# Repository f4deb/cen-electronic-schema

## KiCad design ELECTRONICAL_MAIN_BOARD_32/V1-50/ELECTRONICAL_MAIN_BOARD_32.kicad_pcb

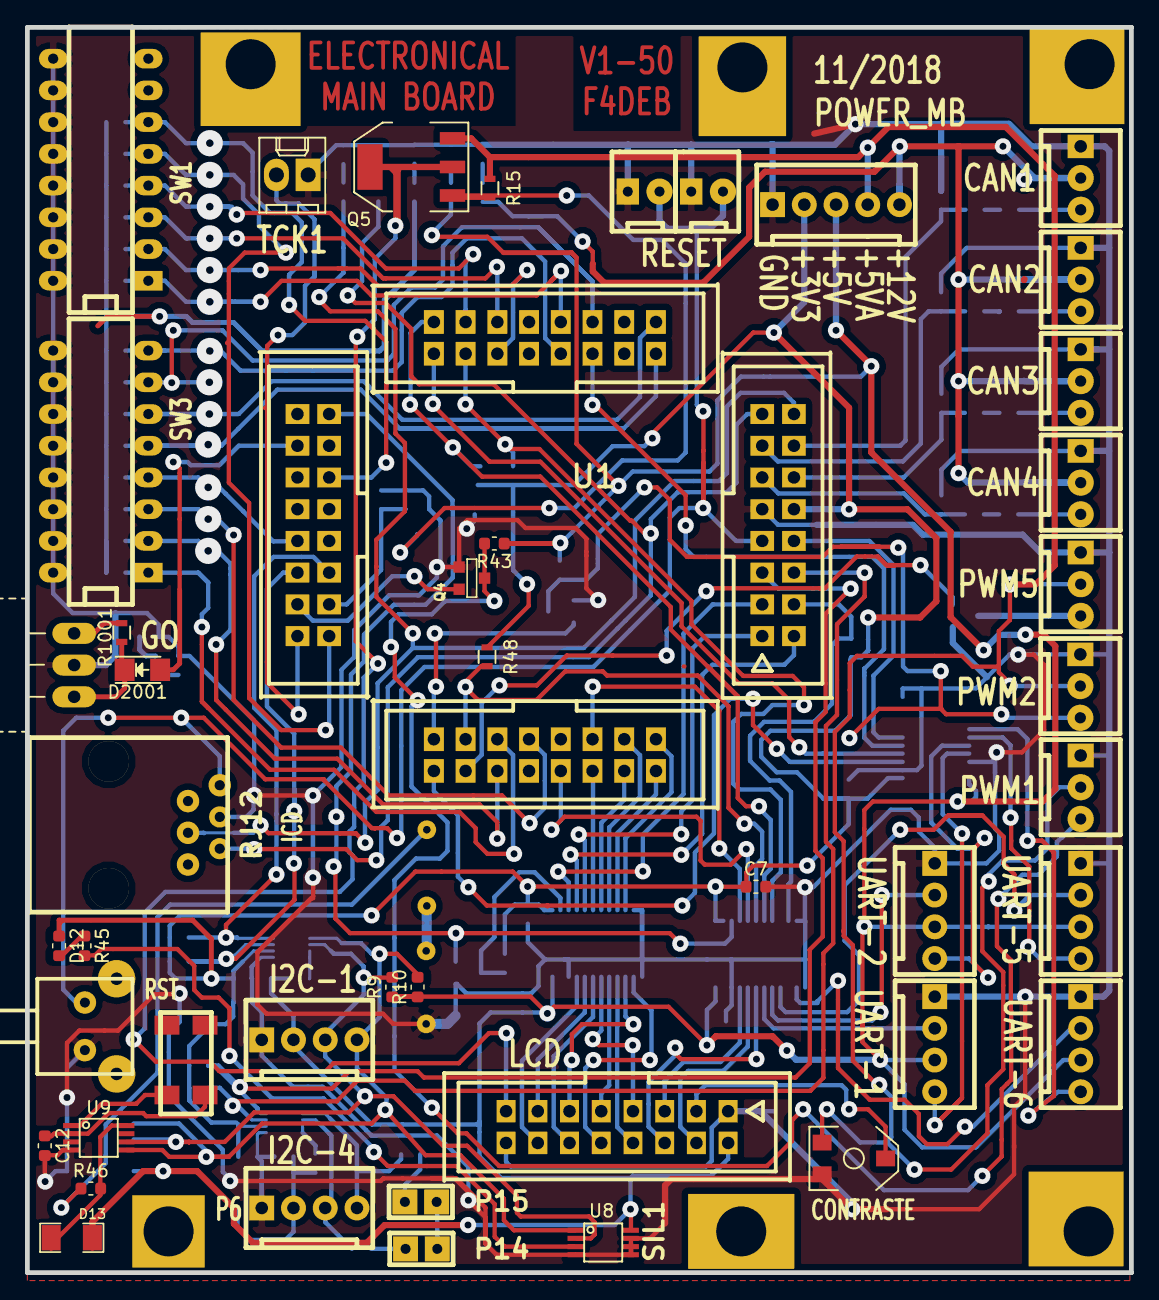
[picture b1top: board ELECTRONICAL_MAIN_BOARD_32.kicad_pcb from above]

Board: 2 copper layers, 88.4 x 99.7 mm, 126 parts (0 on the bottom side), 112 nets.

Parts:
C1, C2, C3, C4, C5, C6, C7, C8, C10, C11: 100n; C_0603_1608Metric
C9, C13: 10F; C-10F
C12: C; C_0603_1608Metric
D1, D2, D3, D4, D5, D7, D8, D9, D10, D11: LED; LED_0603_1608Metric
D12: LED; R_0603_1608Metric
D13: DIODESCH; SM1206
D2001: LED; LED_1206
J1, J2, J3, J4, J6, J7: SIL1; COLONETTE
J5: RJ12; RJ12_E
K1, K2, K3, K4, K5, K6, K7: CONN_3; KK-3
K8: CONN_2; Molex_KK_6410-02
P1: HE10-16; he10-16d
P2, P3, P4, P5, P6, P7: CONN_4; KK-4
P9: CONN_5; KK-5
P10, P11: CONN_2; KK-2
P14, P15: CAVALIER
Q1, Q2, Q3, Q4: BSS123; SOT23EBC
Q5: IRFL9014TRPBF; SOT-223
Q6: 2N7002; SOT-23
R1, R9, R10, R13, R14: 1k; R_0603_1608Metric
R2, R3, R4, R6, R45: 330; R_0603_1608Metric
R5, R16, R17, R18, R19, R20, R21, R22, R23, R24, R25, R26, R27, R28, R29: 10K; R_0603_1608Metric
R7, R8, R11, R12: 2.1k; R_0603_1608Metric
R15, R48, R49, R50, R51: 10k; R_0603
R30, R31, R32, R33: 3.2k; R_0603_1608Metric
R34, R35, R36, R37: 1.5k; R_0603_1608Metric
R38, R39: 220k; R_0603_1608Metric
R40, R41, R42, R43: 4.7k; R_0603_1608Metric
R44: 3..3k; R_0603_1608Metric
R46: 150; R_0603_1608Metric
R47: 100k; R_0603
R1001: 1k; R_0603
RVAR1: 4.7K; POT_SMD
SW1, SW3: SWITCH_X_8; DIP-16__300_ELL
SW2: SW_PUSH_SMALL; SW
U1: PIC32MX795F512H; PIC32½64
U2, U3, U6: 74LVCC3245; SSOP24
U4, U5: PCA9306; VSSOP-8
U7: 24C512; SOIC-8_3.9x4.9mm_P1.27mm
U8: LM75A; SSOP8
U9: PCF8563; SSOP8
U1001: HALL-U18; TO-220_Neutral123_Horizontal_MountedFromLS_LargePads
X1: CRYSTAL1; LFXTAL003000

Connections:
+3V3: C1.1, C2.1, C3.1, C7.1, C8.1, D12.1, J5.2, P9.2, R2.1, R7.1, R8.1, R11.1, R12.1, R16.1, R17.1, R18.1, R19.1, R20.1, R21.1, R22.1, R23.1, R24.1, R25.1, R26.1, R27.1, R28.1, R29.1, R42.1, R48.1, R49.1, R50.1, R51.1, U1.10, U2.1, U2.2, U3.1, U4.2, U5.2, U6.1
+5V: C4.1, C5.1, C6.1, C10.1, C11.1, D13.1, P1.2, P2.3, P3.3, P4.3, P5.3, P6.2, P7.2, P9.3, P14.2, P15.2, R1.1, R9.1, R10.1, R38.1, R39.1, R40.1, R41.1, R43.1, U2.24, U3.24, U6.24, U7.8, U8.8
+5VA: K5.2, K6.2, K7.2, P9.4, Q5.3, R15.1, RVAR1.1
+5VD: R1001.1, U1001.1
+12V: K1.2, K2.2, K3.2, K4.2, P9.5, R44.1
/5vto3v3/D0: U1.60, U6.6
/5vto3v3/D1: U1.61, U6.8
/5vto3v3/D2: U1.62, U6.7
/5vto3v3/D3: U1.63, U6.10
/5vto3v3/D4: U1.64, U6.9
/5vto3v3/D5: U1.1, U6.5
/5vto3v3/D6: U1.2, U6.4
/5vto3v3/D7: U1.3, U6.3
/5vto3v3/E: U1.58, U2.5
/5vto3v3/OC1: Q4.1, U1.46
/5vto3v3/OC1-5V: K5.3, Q4.3, R43.2
/5vto3v3/OC2: Q1.1, U1.49
/5vto3v3/OC2-5V: K6.3, Q1.3, R40.2
/5vto3v3/OC5: Q2.1, U1.52
/5vto3v3/OC5-5V: K7.3, Q2.3, R41.2
/5vto3v3/RS: U1.59, U2.4
/5vto3v3/RW: Q3.1, U1.33, U2.3
/5vto3v3/SCL1: R8.2, U1.44, U4.3
/5vto3v3/SCL4: R12.2, U1.6, U5.3
/5vto3v3/SCL4-5V: P6.3, R13.2, U5.6
/5vto3v3/SDA1: R7.2, U1.43, U4.4
/5vto3v3/SDA4: R11.2, U1.5, U5.4
/5vto3v3/SDA4-5V: P6.4, R14.2, U5.5
/5vto3v3/U1RX: U1.50, U3.3
/5vto3v3/U1RX-5V: P2.4, U3.21
/5vto3v3/U1TX: R48.2, U1.51, U2.6
/5vto3v3/U1TX-5V: P2.2, U2.18
/5vto3v3/U2RX: U1.31, U3.4
/5vto3v3/U2RX-5V: P3.4, U3.20
/5vto3v3/U2TX: R49.2, U1.32, U2.7
/5vto3v3/U2TX-5V: P3.2, U2.17
/5vto3v3/U5RX: U1.21, U3.5
/5vto3v3/U5RX-5V: P4.4, U3.19
/5vto3v3/U5TX: R50.2, U1.29, U2.8
/5vto3v3/U5TX-5V: P4.2, U2.16
/5vto3v3/U6RX: U1.8, U3.6
/5vto3v3/U6RX-5V: P5.4, U3.18
/5vto3v3/U6TX: R51.2, U1.4, U2.10
/5vto3v3/U6TX-5V: P5.2, U2.14
/BD0: P1.7, U6.18
/BD1: P1.8, U6.16
/BD2: P1.9, U6.17
/BD3: P1.10, U6.14
/BD4: P1.11, U6.15
/BD5: P1.12, U6.19
/BD6: P1.13, U6.20
/BD7: P1.14, U6.21
/BE: P1.6, U2.19
/BRS: P1.4, U2.20
/BRW: P1.5, U2.21
/CONT: P1.3, RVAR1.2
/PIC32/CAN1: D7.1, K1.3
/PIC32/CAN2: D8.1, K2.3
/PIC32/CAN3: D9.1, K3.3
/PIC32/CAN4: D10.1, K4.3
/PIC32/GO: D2001.1, R1001.2, U1001.3
/PIC32/LED1: D2.1, R3.2
/PIC32/LED2: D1.1, R4.2
/PIC32/PGEC1: J5.5, R4.1, U1.15
/PIC32/PGED1: J5.4, R3.1, U1.16
/PIC32/RST: J5.1, P10.2, P11.2, SW2.2, U1.7
/PIC32/SW0: R26.2, SW3.1, U1.53
/PIC32/SW1: R27.2, SW3.2, U1.54
/PIC32/SW2: R28.2, SW3.3, U1.55
/PIC32/SW3: R29.2, SW3.4, U1.42
/PIC32/SW4: R16.2, SW3.5, U1.17
/PIC32/SW5: R17.2, SW3.6, U1.18
/PIC32/SW6: R18.2, SW3.7, U1.22
/PIC32/SW7: R19.2, SW3.8, U1.23
/PIC32/SW8: R20.2, SW1.1, U1.24
/PIC32/SW9: R21.2, SW1.2, U1.27
/PIC32/SW10: R22.2, SW1.3, U1.28
/PIC32/SW11: R23.2, SW1.4, U1.30
/PIC32/SW12: R24.2, SW1.5, U1.47
/PIC32/SW13: R25.2, SW1.6, U1.37
/PIC32/T1CK: K8.2, U1.48
/RETRO: P1.15, Q5.2, Q5.4
/SCL1-5V: P7.3, R9.2, U4.6, U7.6, U8.2, U9.6
/SDA1-5V: P7.4, R10.2, U4.5, U7.5, U8.1, U9.5
GND: C1.2, C2.2, C3.2, C4.2, C5.2, C6.2, C7.2, C8.2, C9.2, C10.2, C11.2, C12.2, D1.2, D2.2, D3.2, D4.2, D11.2, J5.3, K1.1, K2.1, K3.1, K4.1, K5.1, K6.1, K7.1, K8.1, P1.1, P1.16, P2.1, P3.1, P4.1, P5.1, P6.1, P7.1, P9.1, P10.1, P11.1, Q1.2, Q2.2, Q3.2, Q4.2, Q6.2, R5.2, R6.2, R34.2, R35.2, R36.2, R37.2, R47.2, RVAR1.3, SW1.9, SW1.10, SW1.11, SW1.12, SW1.13, SW1.14, SW1.15, SW1.16, SW2.1, SW3.9, SW3.10, SW3.11, SW3.12, SW3.13, SW3.14, SW3.15, SW3.16, U1.9, U2.11, U2.12, U2.13, U2.22, U3.2, U3.11, U3.12, U3.13, U3.22, U4.1, U5.1, U6.11, U6.12, U6.13, U6.22, U7.1, U7.2, U7.3, U7.4, U8.4, U8.5, U8.6, U8.7, U9.4, U1001.2
unnamed: C12.1, U9.2, X1.1
unnamed: C13.1, R46.1
unnamed: C9.1, C13.2
unnamed: D3.1, R1.2
unnamed: D4.1, R2.2
unnamed: D5.2, R6.1
unnamed: D7.2, R30.1
unnamed: D8.2, R31.1
unnamed: D9.2, R32.1
unnamed: D10.2, R33.1
unnamed: D11.1, R44.2
unnamed: D12.2, R45.1
unnamed: D13.2, R46.2, U9.8
unnamed: D5.1, D2001.2, R5.1, U1.36
unnamed: P14.1, R13.1
unnamed: P15.1, R14.1
unnamed: Q3.3, R42.2, U6.2
unnamed: Q5.1, Q6.3, R15.2
unnamed: Q6.1, R47.1, U1.45
unnamed: R30.2, R34.1, U1.14
unnamed: R31.2, R35.1, U1.13
unnamed: R32.2, R36.1, U1.12
unnamed: R33.2, R37.1, U1.11
unnamed: R38.2, U4.7, U4.8
unnamed: R39.2, U5.7, U5.8
unnamed: R45.2, U8.3
unnamed: U9.1, X1.2

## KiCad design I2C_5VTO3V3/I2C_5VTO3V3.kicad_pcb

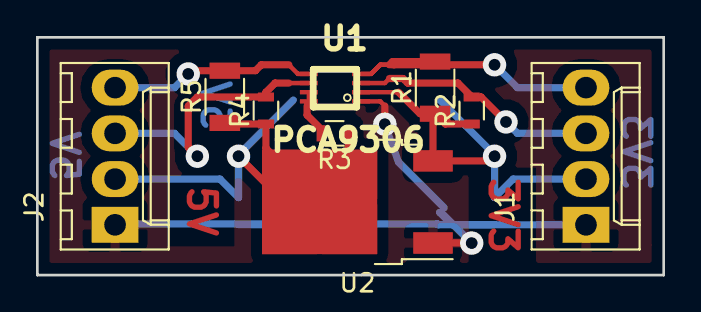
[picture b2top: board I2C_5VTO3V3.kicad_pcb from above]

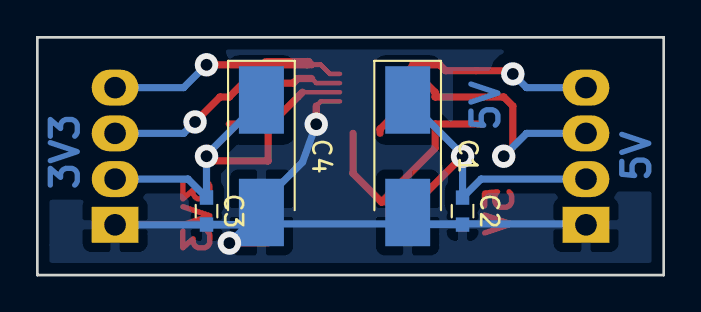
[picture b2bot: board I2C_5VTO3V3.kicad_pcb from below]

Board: 2 copper layers, 34.8 x 13.2 mm, 13 parts (4 on the bottom side), 8 nets.

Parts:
C1, C4: 10U/10V; CP_Tantalum_Case-C_EIA-6032-28_Hand
C2, C3: 100n; C_0603
J1, J2: Conn_01x04; Molex_KK-6410-04_04x2.54mm_Straight
R1, R5: 2.1k; R_1206
R2, R4: 2.1k; R_0603
R3: 220k; R_0603
U1: PCA9306; VSSOP-8
U2: LM1117; TO-252-2

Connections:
+3V3: C3.1, C4.1, J1.2, R1.1, R2.1, U1.2, U2.3
+5V: C1.1, C2.1, J2.2, R3.1, R4.1, R5.1, U2.2
GND: C1.2, C2.2, C3.2, C4.2, J1.1, J2.1, U1.1, U2.1
unnamed: J1.3, R2.2, U1.3
unnamed: J1.4, R1.2, U1.4
unnamed: J2.3, R4.2, U1.6
unnamed: J2.4, R5.2, U1.5
unnamed: R3.2, U1.7, U1.8

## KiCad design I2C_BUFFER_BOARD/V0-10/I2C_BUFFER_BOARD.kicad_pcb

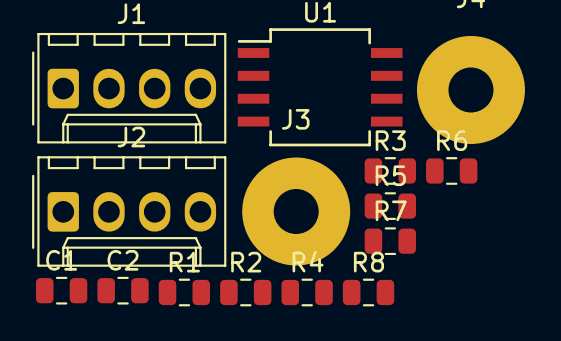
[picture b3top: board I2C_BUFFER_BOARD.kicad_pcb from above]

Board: 2 copper layers, 15 parts (0 on the bottom side), 10 nets, no tracks yet.

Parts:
C1: 100n; C_0805_2012Metric
C2: 1u; C_0805_2012Metric
J1, J2: Conn_01x04_Male; Molex_KK-254_AE-6410-04A_1x04_P2.54mm_Vertical
J3, J4: Conn_01x01_Female; SolderWirePad_1x01_Drill2.5mm
R1, R2, R3, R4: R; R_0805_2012Metric
R5, R6, R7, R8: 0; R_0805_2012Metric
U1: P82B715; SO-8_5.3x6.2mm_P1.27mm

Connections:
unnamed: C1.1, C2.1, J1.2, J2.2, R5.1, R6.1, R7.1, R8.1, U1.8
unnamed: C1.2, C2.2, J1.1, J2.1, U1.4
unnamed: J1.3, R2.2, U1.3
unnamed: J1.4, R1.2, U1.2
unnamed: J2.3, R4.2, U1.6
unnamed: J2.4, R3.2, U1.7
unnamed: R1.1, R5.2
unnamed: R2.1, R6.2
unnamed: R3.1, R7.2
unnamed: R4.1, R8.2

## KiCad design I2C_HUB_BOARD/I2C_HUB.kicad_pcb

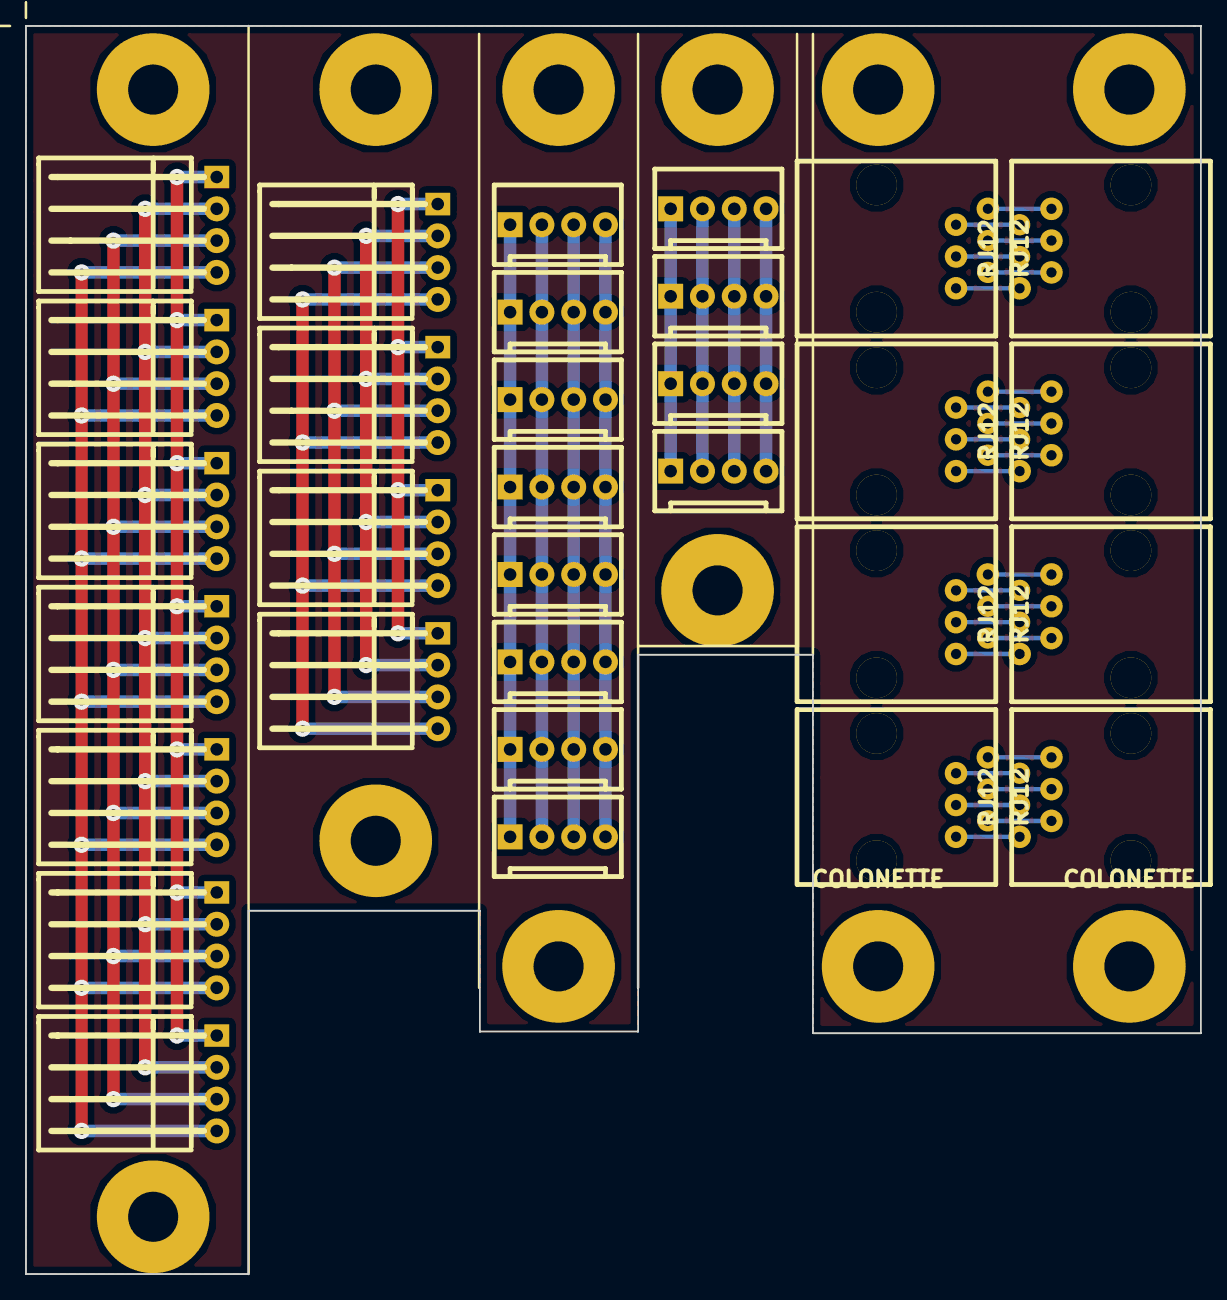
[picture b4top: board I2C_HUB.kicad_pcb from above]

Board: 2 copper layers, 93.9 x 99.7 mm, 43 parts (0 on the bottom side), 40 nets.

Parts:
J1001, J1002, J1003, J1004, J1005, J1006, J1007, J1008: RJ12; RJ12_E
K1001, K1002, K1003, K1004: COLONETTE
P1001, P1002, P1011, P1012, P1021, P1022, P1027, P1028: CONN_01X01; COLONETTE
P1003, P1004, P1005, P1006, P1007, P1008, P1009, P1010, P1023, P1024, P1025, P1026: CONN_01X04; KK-4
P1013, P1015, P1016, P1017, P1018, P1019, P1020, P1029, P1030, P1031, P1032: CONN_01X04; KK-4-H

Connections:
unnamed: J1001.1, J1002.6
unnamed: J1001.2, J1002.5
unnamed: J1001.3, J1002.4
unnamed: J1001.4, J1002.3
unnamed: J1001.5, J1002.2
unnamed: J1001.6, J1002.1
unnamed: J1003.1, J1004.6
unnamed: J1003.2, J1004.5
unnamed: J1003.3, J1004.4
unnamed: J1003.4, J1004.3
unnamed: J1003.5, J1004.2
unnamed: J1003.6, J1004.1
unnamed: J1005.1, J1006.6
unnamed: J1005.2, J1006.5
unnamed: J1005.3, J1006.4
unnamed: J1005.4, J1006.3
unnamed: J1005.5, J1006.2
unnamed: J1005.6, J1006.1
unnamed: J1007.1, J1008.6
unnamed: J1007.2, J1008.5
unnamed: J1007.3, J1008.4
unnamed: J1007.4, J1008.3
unnamed: J1007.5, J1008.2
unnamed: J1007.6, J1008.1
unnamed: P1003.1, P1004.1, P1005.1, P1006.1, P1007.1, P1008.1, P1009.1, P1010.1
unnamed: P1003.2, P1004.2, P1005.2, P1006.2, P1007.2, P1008.2, P1009.2, P1010.2
unnamed: P1003.3, P1004.3, P1005.3, P1006.3, P1007.3, P1008.3, P1009.3, P1010.3
unnamed: P1003.4, P1004.4, P1005.4, P1006.4, P1007.4, P1008.4, P1009.4, P1010.4
unnamed: P1013.1, P1015.1, P1016.1, P1017.1, P1018.1, P1019.1, P1020.1
unnamed: P1013.2, P1015.2, P1016.2, P1017.2, P1018.2, P1019.2, P1020.2
unnamed: P1013.3, P1015.3, P1016.3, P1017.3, P1018.3, P1019.3, P1020.3
unnamed: P1013.4, P1015.4, P1016.4, P1017.4, P1018.4, P1019.4, P1020.4
unnamed: P1023.1, P1024.1, P1025.1, P1026.1
unnamed: P1023.2, P1024.2, P1025.2, P1026.2
unnamed: P1023.3, P1024.3, P1025.3, P1026.3
unnamed: P1023.4, P1024.4, P1025.4, P1026.4
unnamed: P1029.1, P1030.1, P1031.1, P1032.1
unnamed: P1029.2, P1030.2, P1031.2, P1032.2
unnamed: P1029.3, P1030.3, P1031.3, P1032.3
unnamed: P1029.4, P1030.4, P1031.4, P1032.4

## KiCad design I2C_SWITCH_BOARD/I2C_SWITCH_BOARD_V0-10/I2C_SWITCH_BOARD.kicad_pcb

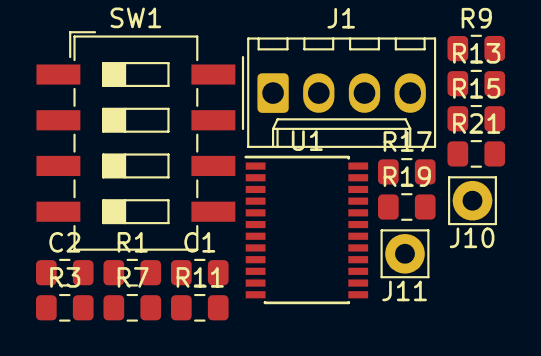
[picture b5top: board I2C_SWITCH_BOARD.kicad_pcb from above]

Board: 2 copper layers, 17 parts (0 on the bottom side), 16 nets, no tracks yet.

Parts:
C1: 100n; C_0805_2012Metric_Pad1.15x1.40mm_HandSolder
C2: 1u; C_0805_2012Metric_Pad1.15x1.40mm_HandSolder
J1: Conn_01x04_Male; Molex_KK-254_AE-6410-04A_1x04_P2.54mm_Vertical
J10, J11: Conn_01x01_Female; Pin_D1.1mm_L8.5mm_W2.5mm_FlatFork
R1, R7, R9, R11, R13, R15, R17, R19, R21: 2.1k; R_0805_2012Metric_Pad1.15x1.40mm_HandSolder
R3: 10k; R_0805_2012Metric_Pad1.15x1.40mm_HandSolder
SW1: SW_DIP_x04; SW_DIP_SPSTx04_Slide_6.7x11.72mm_W8.61mm_P2.54mm_LowProfile
U1: TCA9548APWR; TSSOP-24_4.4x7.8mm_P0.65mm

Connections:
unnamed: C1.1, C2.1, J1.1
unnamed: C1.2, C2.2, J1.2, R1.1, R3.2, R7.1, R9.1, R11.1, R13.1, R15.1, R17.1, R19.1, R21.1, SW1.1, SW1.2, SW1.3, U1.12, U1.24
unnamed: J1.3, R1.2, U1.22
unnamed: J1.4, U1.23
unnamed: R7.2, U1.5
unnamed: R9.2, U1.7
unnamed: R11.2, U1.9
unnamed: R13.2, U1.11
unnamed: R15.2, U1.14
unnamed: R17.2, U1.16
unnamed: R19.2, U1.18
unnamed: R21.2, U1.20
unnamed: SW1.8, U1.21
unnamed: R3.1, U1.3
unnamed: SW1.7, U1.2
unnamed: SW1.6, U1.1

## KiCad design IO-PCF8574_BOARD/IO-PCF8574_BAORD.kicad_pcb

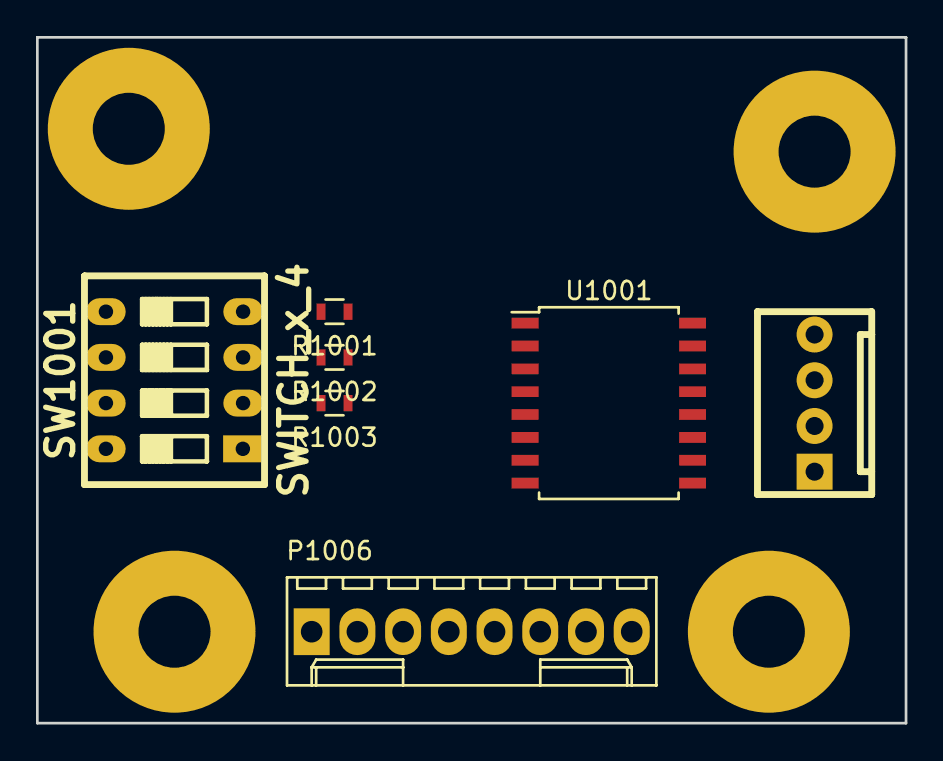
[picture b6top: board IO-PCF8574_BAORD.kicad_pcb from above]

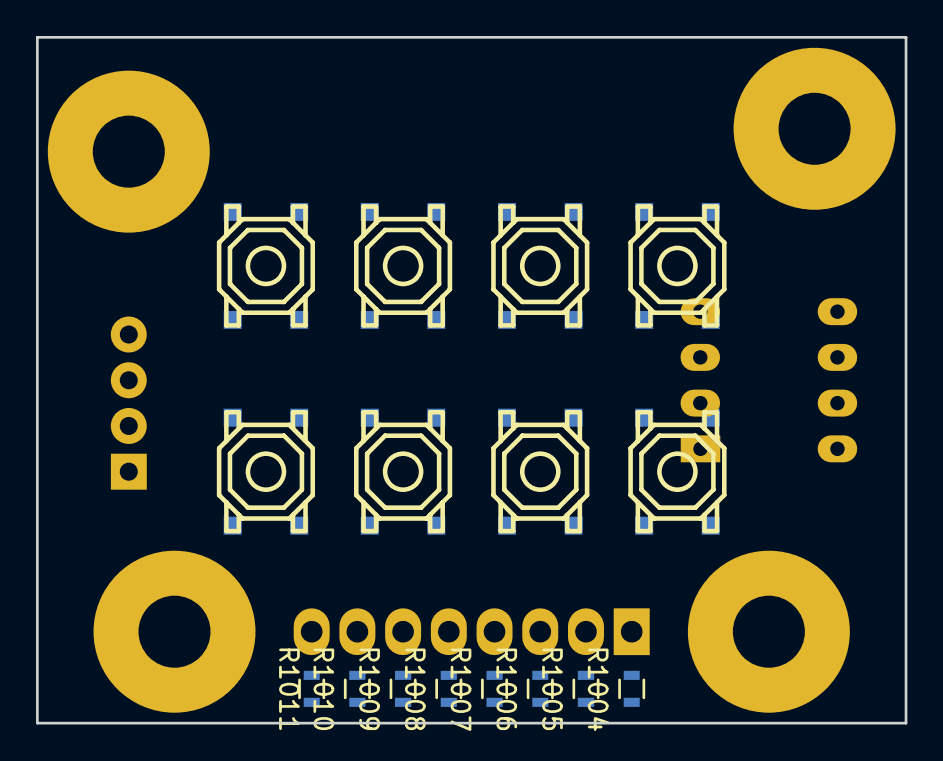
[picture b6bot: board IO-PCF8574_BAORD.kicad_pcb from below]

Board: 2 copper layers, 48.3 x 38.1 mm, 27 parts (16 on the bottom side), 15 nets, no tracks yet.

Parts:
P1001, P1003, P1004, P1005: CONN_01X01; COLONETTE
P1002: CONN_01X04; KK-4
P1006: CONN_01X08; Molex_KK-6410-08_08x2.54mm_Straight
R1001, R1002, R1003, R1004, R1005, R1006, R1007, R1008, R1009, R1010, R1011: 100k; R_0603
SW1001: SWITCH_x_4; dip_4-300
SW1002, SW1003, SW1004, SW1005, SW1006, SW1007, SW1008, SW1009: SW_PUSH_SMALL; smd_push2
U1001: PCF8574A; SOIC-16W_7.5x10.3mm_Pitch1.27mm

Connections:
+5VD: P1002.2, R1001.1, R1002.1, R1003.1, R1004.1, R1005.1, R1006.1, R1007.1, R1008.1, R1009.1, R1010.1, R1011.1, U1001.16
GND: P1002.1, SW1001.5, SW1001.6, SW1001.7, SW1001.8, SW1002.2, SW1003.2, SW1004.2, SW1005.2, SW1006.2, SW1007.2, SW1008.2, SW1009.2, U1001.8
unnamed: P1002.3, U1001.14
unnamed: P1002.4, U1001.15
unnamed: P1006.1, R1004.2, SW1002.1, U1001.4
unnamed: P1006.2, R1005.2, SW1003.1, U1001.5
unnamed: P1006.3, R1006.2, SW1004.1, U1001.6
unnamed: P1006.4, R1007.2, SW1005.1, U1001.7
unnamed: P1006.5, R1008.2, SW1006.1, U1001.9
unnamed: P1006.6, R1009.2, SW1007.1, U1001.10
unnamed: P1006.7, R1010.2, SW1008.1, U1001.11
unnamed: P1006.8, R1011.2, SW1009.1, U1001.12
unnamed: R1001.2, SW1001.4, U1001.1
unnamed: R1002.2, SW1001.3, U1001.2
unnamed: R1003.2, SW1001.2, U1001.3
